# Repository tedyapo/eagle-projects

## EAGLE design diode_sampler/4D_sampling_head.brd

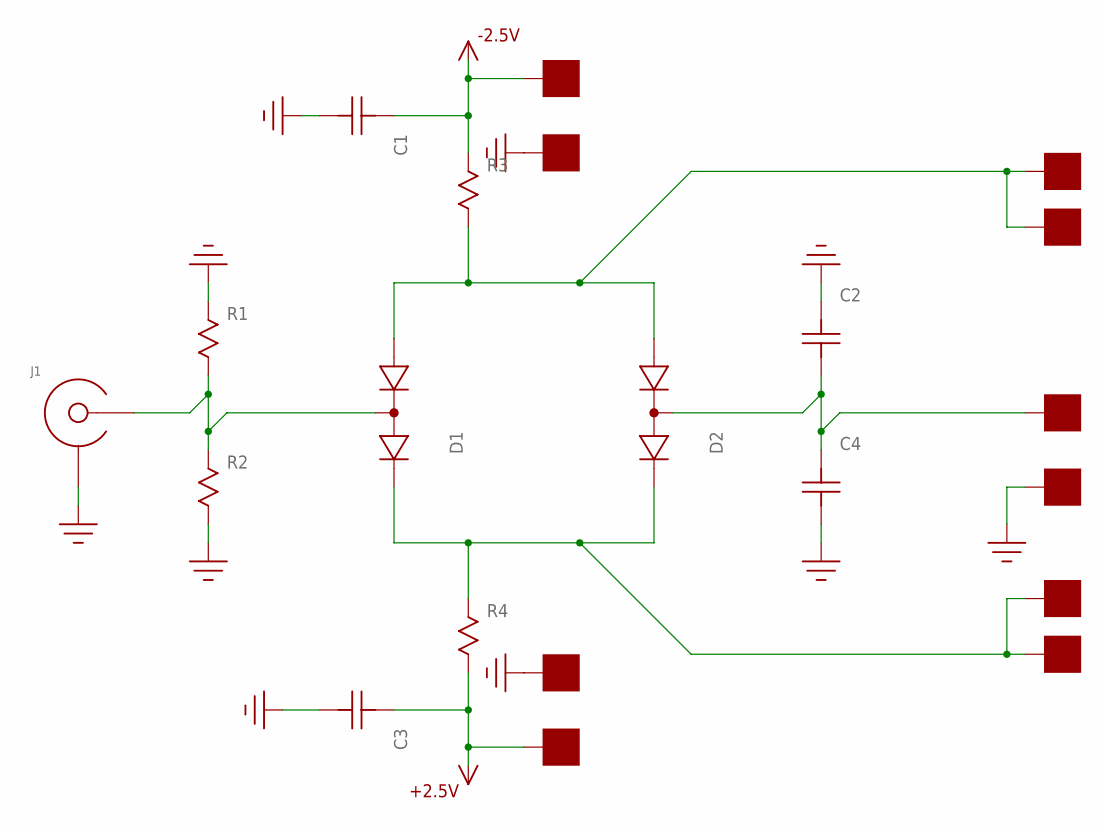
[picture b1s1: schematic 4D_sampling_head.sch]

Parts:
C1, C2, C3, C4: C0603
D1: MMBD352LT1G; SOT-23
D2: MMBD353LT1G; SOT-23
J1: EDGE_LAUNCH_JACK; EDGE_LAUNCH_RF_CON
R1, R2, R3, R4: R0603
U$11, U$12, U$13, U$14: PAD50MIL; PAD_50MIL
U$15, U$16, U$18, U$19, U$20, U$21: PAD100MIL; PAD_100MIL

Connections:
+2.5V: C3.P$2, R4.P$2, U$19.P$1
-2.5V: C1.P$2, R3.P$1, U$18.P$1
GND: C1.P$1, C2.P$2, C3.P$1, C4.P$1, J1.GND@1 (SHIELD), J1.GND@2 (SHIELD), J1.GND@3 (SHIELD), J1.GND@4 (SHIELD), J1.GND@5 (SHIELD), J1.GND@6 (SHIELD), J1.GND@7 (SHIELD), J1.GND@8 (SHIELD), J1.GND@9 (SHIELD), J1.GND@10 (SHIELD), J1.GND@11 (SHIELD), J1.GND@12 (SHIELD), J1.SHIELD@1 (SHIELD), J1.SHIELD@2 (SHIELD), R1.P$1, R2.P$2, U$16.P$1, U$20.P$1, U$21.P$1
unnamed: D1.3 (COMMON), J1.CENTER, R1.P$2, R2.P$1
unnamed: D1.2 (CATHODE), D2.1 (CATHODE), R4.P$1, U$12.P$1, U$14.P$1
unnamed: D1.1 (ANODE), D2.2 (ANODE), R3.P$2, U$11.P$1, U$13.P$1
unnamed: C2.P$1, C4.P$2, D2.3 (COMMON), U$15.P$1

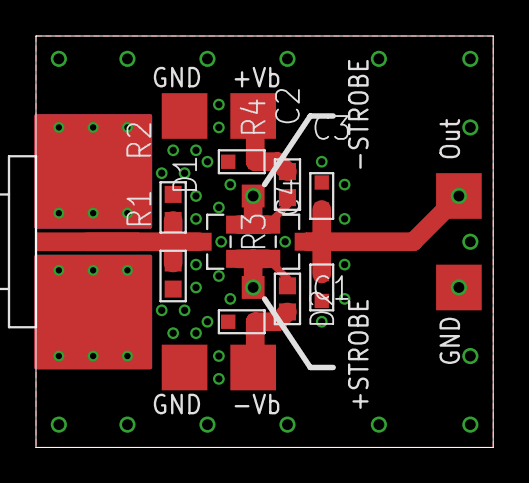
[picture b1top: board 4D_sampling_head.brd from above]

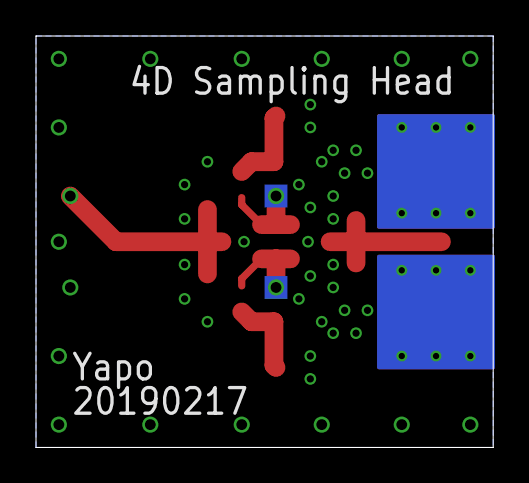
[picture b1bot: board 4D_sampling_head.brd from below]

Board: 2 copper layers, 25.4 x 22.9 mm, 21 parts (2 on the bottom side), 7 nets.

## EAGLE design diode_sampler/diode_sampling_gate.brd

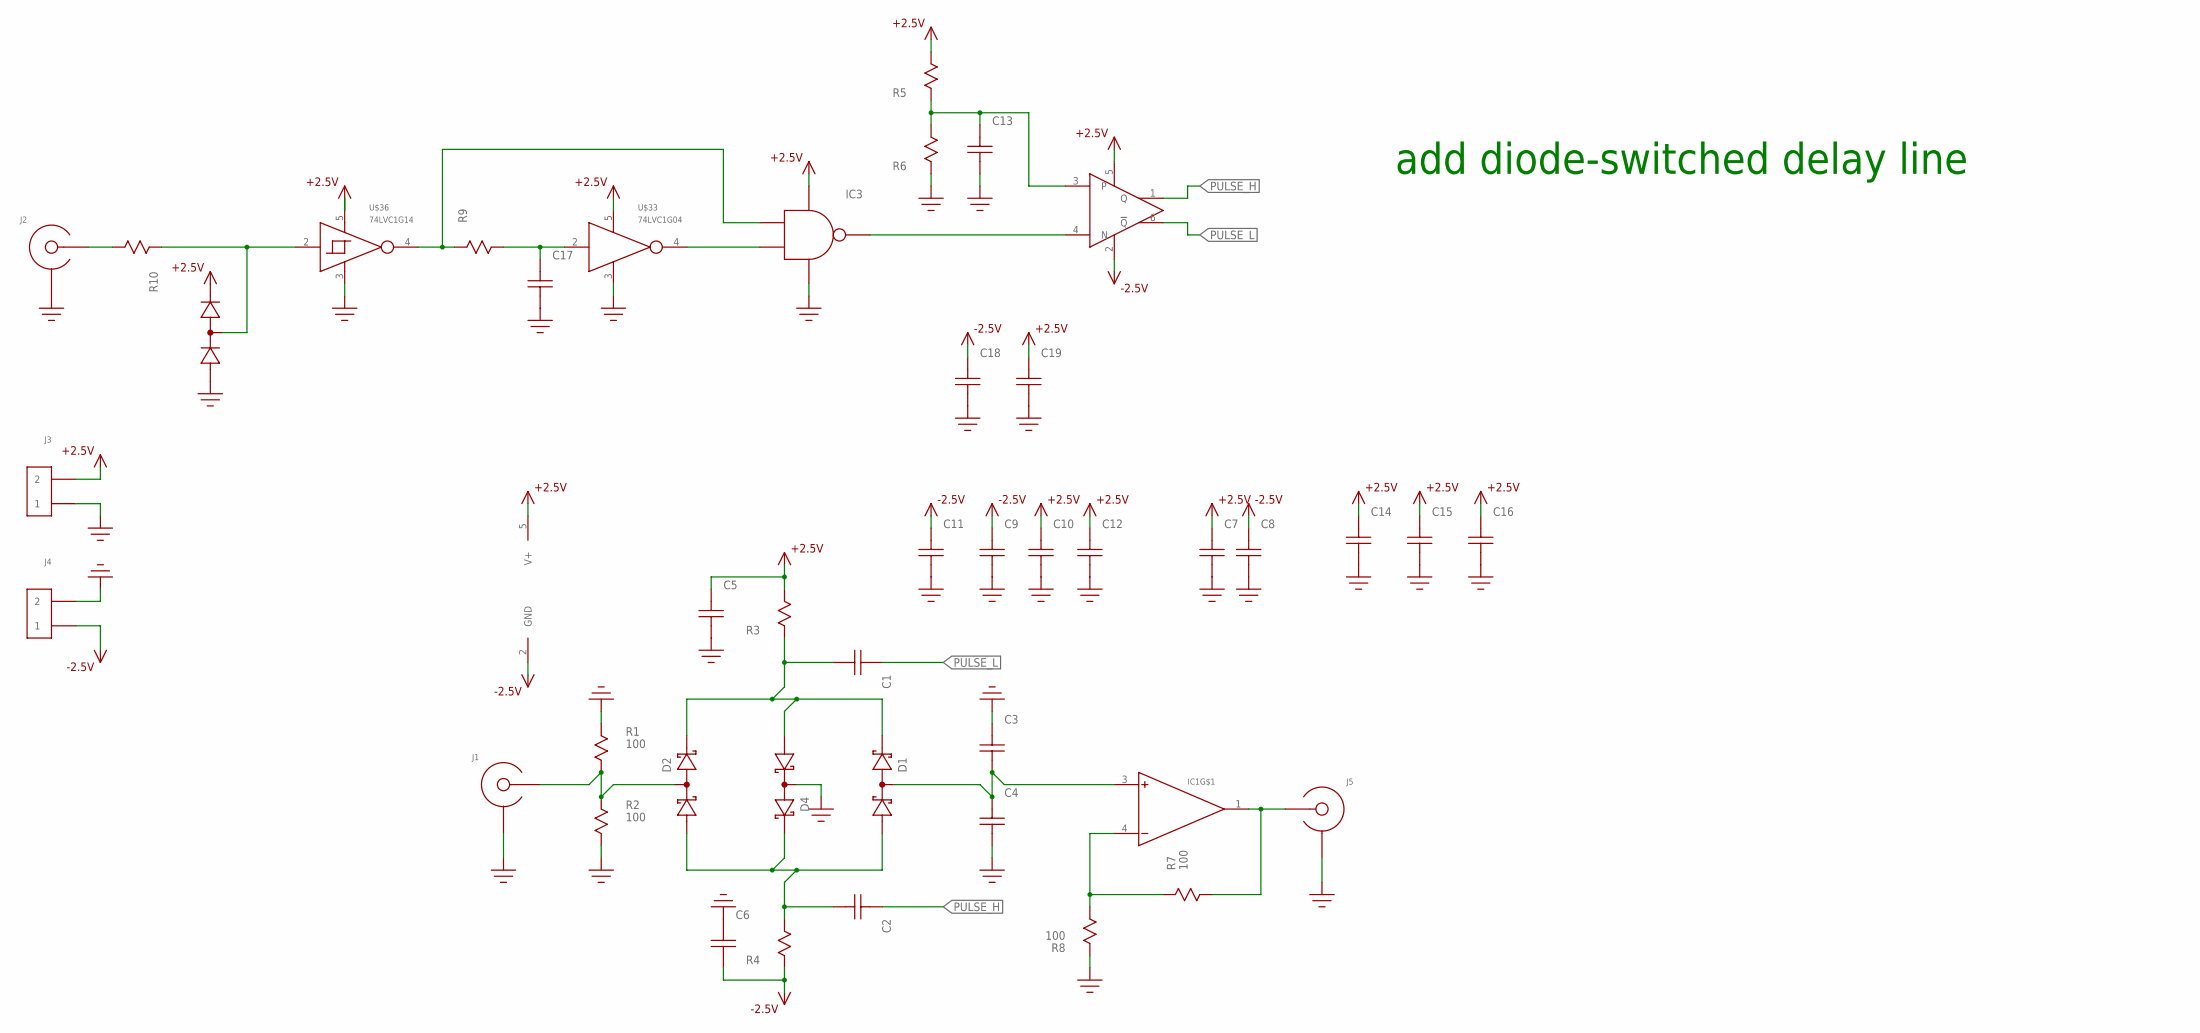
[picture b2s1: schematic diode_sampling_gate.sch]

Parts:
C1, C2, C3, C4, C5, C6, C9, C10, C13, C14, C15, C16, C17: C0603
C7, C8: C; C0402
C11, C12, C18, C19: C0805; 0805
D1, D2, D4: BAS40-04; SOT-23
IC1: MCP6V81; SOT23-5
IC2: ADCMP606; SC70-6
IC3: 74LVC1G00; SOT23-5
J1, J2, J5: EDGE_LAUNCH_JACK; EDGE_LAUNCH_RF_CON
J3, J4: HEADER_2PIN
R1, R2, R7, R8: 100; R0603
R3, R4, R5, R6, R9, R10: R0603
U$33: 74LVC1G04; SOT23-5
U$36: 74LVC1G14; SOT23-5
U$46: MMBD7000L; SOT-23

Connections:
+2.5V: C5.P$2, C7.2, C10.P$2, C12.P$2, C14.P$2, C15.P$2, C16.P$2, C19.P$2, IC1.5 (V+), IC2.5 (VCC), IC3.5 (VCC), J3.2, R3.P$2, R5.P$2, U$33.5 (VCC), U$36.5 (VCC), U$46.2 (CATHODE)
-2.5V: C6.P$1, C8.2, C9.P$2, C11.P$2, C18.P$2, IC1.2 (GND), IC2.2 (VEE), J4.1, R4.P$1
GND: C3.P$2, C4.P$1, C5.P$1, C6.P$2, C7.1, C8.1, C9.P$1, C10.P$1, C11.P$1, C12.P$1, C13.P$1, C14.P$1, C15.P$1, C16.P$1, C17.P$1, C18.P$1, C19.P$1, D4.3 (COMMON), IC3.3 (GND), J1.GND@1 (SHIELD), J1.GND@2 (SHIELD), J1.GND@3 (SHIELD), J1.GND@4 (SHIELD), J1.GND@5 (SHIELD), J1.GND@6 (SHIELD), J1.GND@7 (SHIELD), J1.GND@8 (SHIELD), J1.GND@9 (SHIELD), J1.GND@10 (SHIELD), J1.GND@11 (SHIELD), J1.GND@12 (SHIELD), J1.SHIELD@1 (SHIELD), J1.SHIELD@2 (SHIELD), J2.GND@1 (SHIELD), J2.GND@2 (SHIELD), J2.GND@3 (SHIELD), J2.GND@4 (SHIELD), J2.GND@5 (SHIELD), J2.GND@6 (SHIELD), J2.GND@7 (SHIELD), J2.GND@8 (SHIELD), J2.GND@9 (SHIELD), J2.GND@10 (SHIELD), J2.GND@11 (SHIELD), J2.GND@12 (SHIELD), J2.SHIELD@1 (SHIELD), J2.SHIELD@2 (SHIELD), J3.1, J4.2, J5.GND@1 (SHIELD), J5.GND@2 (SHIELD), J5.GND@3 (SHIELD), J5.GND@4 (SHIELD), J5.GND@5 (SHIELD), J5.GND@6 (SHIELD), J5.GND@7 (SHIELD), J5.GND@8 (SHIELD), J5.GND@9 (SHIELD), J5.GND@10 (SHIELD), J5.GND@11 (SHIELD), J5.GND@12 (SHIELD), J5.SHIELD@1 (SHIELD), J5.SHIELD@2 (SHIELD), R1.P$1, R2.P$2, R6.P$1, R8.P$1, U$33.3 (GND), U$36.3 (GND), U$46.1 (ANODE)
unnamed: D2.3 (COMMON), J1.CENTER, R1.P$2, R2.P$1
unnamed: C13.P$2, IC2.3, R5.P$1, R6.P$2
unnamed: C1.P$1, D1.2 (CATHODE), D2.2 (CATHODE), D4.1 (ANODE), R3.P$1
unnamed: IC2.4 (N), IC3.4 (Y)
unnamed: C2.P$1, D1.1 (ANODE), D2.1 (ANODE), D4.2 (CATHODE), R4.P$2
unnamed: IC1.4 (-), R7.P$1, R8.P$2
unnamed: IC1.1 (OUT), J5.CENTER, R7.P$2
unnamed: IC3.1 (B), U$33.4 (OUT)
unnamed: J2.CENTER, R10.P$2
unnamed: C3.P$1, C4.P$2, D1.3 (COMMON), IC1.3 (+)
unnamed: IC3.2 (A), R9.P$1, U$36.4 (OUT)
unnamed: C17.P$2, R9.P$2, U$33.2 (IN)
unnamed: R10.P$1, U$36.2 (IN), U$46.3 (COMMON)
PULSE_H: C2.P$2, IC2.1 (Q)
PULSE_L: C1.P$2, IC2.6 (!Q!)

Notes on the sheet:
add diode-switched delay line

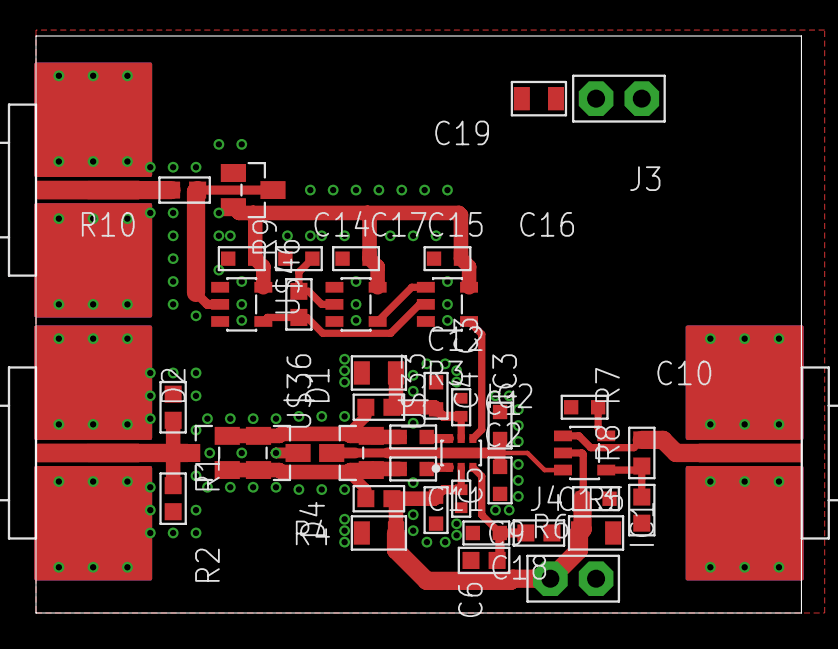
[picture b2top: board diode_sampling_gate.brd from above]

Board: 2 copper layers, 42.5 x 32.1 mm, 43 parts (0 on the bottom side), 18 nets.

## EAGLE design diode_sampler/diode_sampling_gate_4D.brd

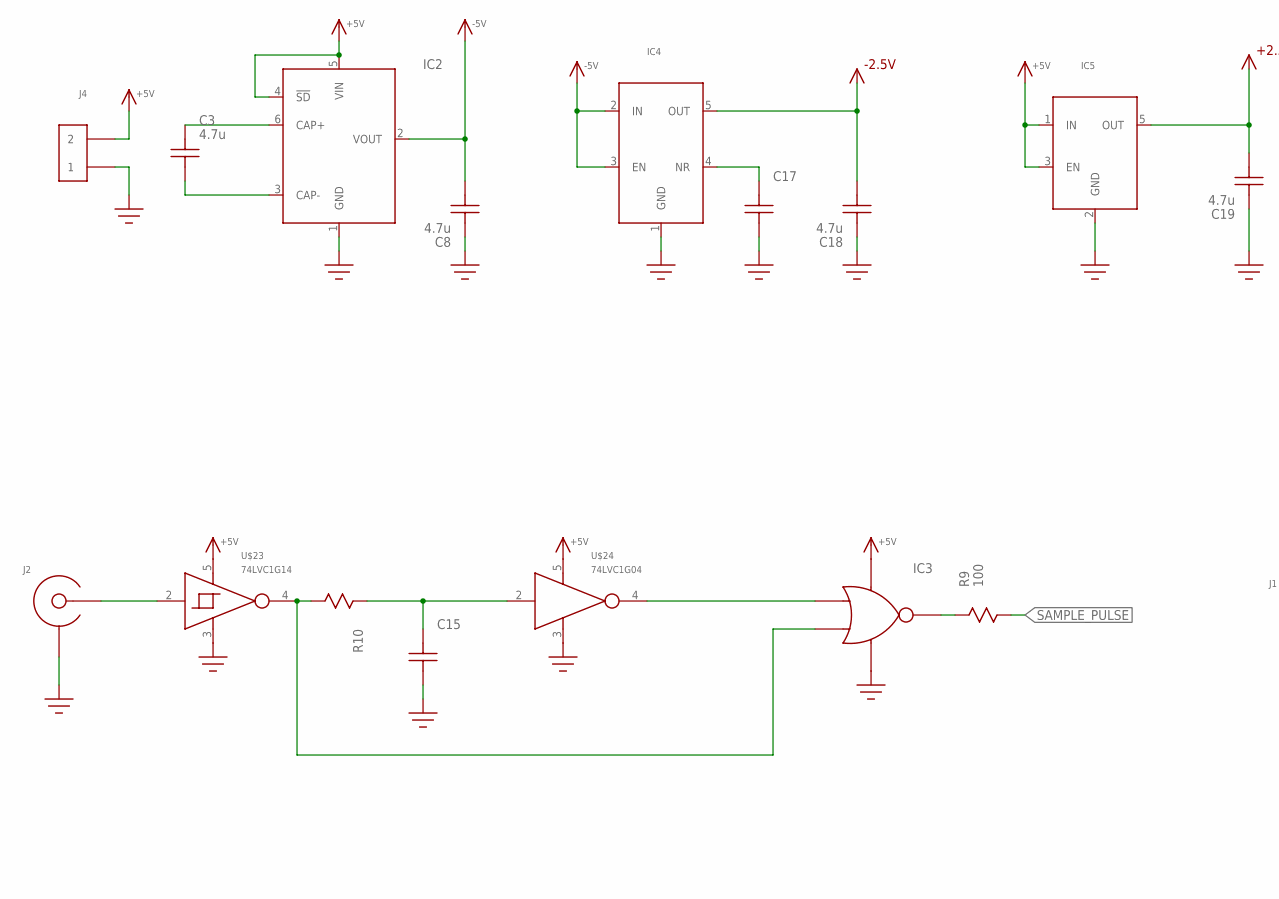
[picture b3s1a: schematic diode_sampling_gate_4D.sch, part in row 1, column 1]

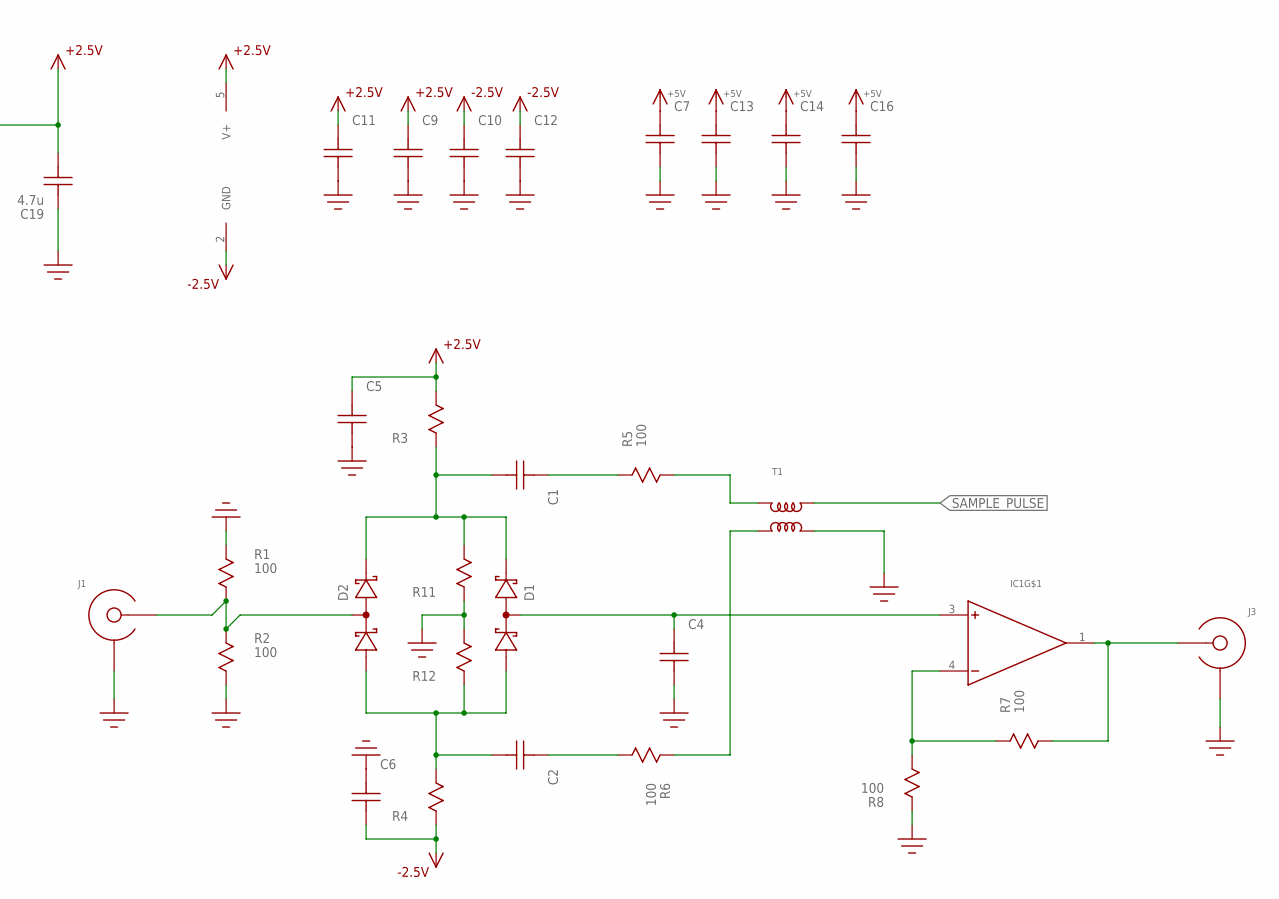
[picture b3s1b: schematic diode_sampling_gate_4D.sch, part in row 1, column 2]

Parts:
C1, C2, C4, C5, C6, C7, C9, C10, C13, C14, C15, C17: C0603
C3, C8, C18, C19: 4.7u; 0805
C11, C12, C16: C0805; 0805
D1, D2: BAS40-04; SOT-23
IC1: MCP6V81; SOT23-5
IC2: LM2664; SOT23-6
IC3: 74LVC1G02; SOT23-5
IC4: TPS723XX; SOT23-5
IC5: LP5907; SOT23-5
J1, J2, J3: EDGE_LAUNCH_JACK; EDGE_LAUNCH_RF_CON
J4: HEADER_2PIN
R1, R2, R5, R6, R7, R8, R9: 100; R0603
R3, R4, R10, R11, R12: R0603
T1: MABA007159; MABAES0061
U$23: 74LVC1G14; SOT23-5
U$24: 74LVC1G04; SOT23-5

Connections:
+2.5V: C5.P$2, C9.P$2, C11.P$2, C19.P$1, IC1.5 (V+), IC5.5 (OUT), R3.P$2
+5V: C7.P$2, C13.P$2, C14.P$2, C16.P$2, IC2.4 (!SD!), IC2.5 (VIN), IC3.5 (VCC), IC5.1 (IN), IC5.3 (EN), J4.2, U$23.5 (VCC), U$24.5 (VCC)
-2.5V: C6.P$1, C10.P$2, C12.P$2, C18.P$1, IC1.2 (GND), IC4.5 (OUT), R4.P$1
-5V: C8.P$1, IC2.2 (VOUT), IC4.2 (IN), IC4.3 (EN)
GND: C4.P$1, C5.P$1, C6.P$2, C7.P$1, C8.P$2, C9.P$1, C10.P$1, C11.P$1, C12.P$1, C13.P$1, C14.P$1, C15.P$1, C16.P$1, C17.P$1, C18.P$2, C19.P$2, IC2.1 (GND), IC3.3 (GND), IC4.1 (GND), IC5.2 (GND), J1.GND@1 (SHIELD), J1.GND@2 (SHIELD), J1.GND@3 (SHIELD), J1.GND@4 (SHIELD), J1.GND@5 (SHIELD), J1.GND@6 (SHIELD), J1.GND@7 (SHIELD), J1.GND@8 (SHIELD), J1.GND@9 (SHIELD), J1.GND@10 (SHIELD), J1.GND@11 (SHIELD), J1.GND@12 (SHIELD), J1.SHIELD@1 (SHIELD), J1.SHIELD@2 (SHIELD), J2.GND@1 (SHIELD), J2.GND@2 (SHIELD), J2.GND@3 (SHIELD), J2.GND@4 (SHIELD), J2.GND@5 (SHIELD), J2.GND@6 (SHIELD), J2.GND@7 (SHIELD), J2.GND@8 (SHIELD), J2.GND@9 (SHIELD), J2.GND@10 (SHIELD), J2.GND@11 (SHIELD), J2.GND@12 (SHIELD), J2.SHIELD@1 (SHIELD), J2.SHIELD@2 (SHIELD), J3.GND@1 (SHIELD), J3.GND@2 (SHIELD), J3.GND@3 (SHIELD), J3.GND@4 (SHIELD), J3.GND@5 (SHIELD), J3.GND@6 (SHIELD), J3.GND@7 (SHIELD), J3.GND@8 (SHIELD), J3.GND@9 (SHIELD), J3.GND@10 (SHIELD), J3.GND@11 (SHIELD), J3.GND@12 (SHIELD), J3.SHIELD@1 (SHIELD), J3.SHIELD@2 (SHIELD), J4.1, R1.P$1, R2.P$2, R8.P$1, R11.P$1, R12.P$2, T1.3, U$23.3 (GND), U$24.3 (GND)
unnamed: D2.3 (COMMON), J1.CENTER, R1.P$2, R2.P$1
unnamed: C1.P$2, R5.P$1
unnamed: C1.P$1, D1.2 (CATHODE), D2.2 (CATHODE), R3.P$1, R11.P$2
unnamed: IC3.2 (B), R10.P$2, U$23.4 (OUT)
unnamed: C2.P$1, D1.1 (ANODE), D2.1 (ANODE), R4.P$2, R12.P$1
unnamed: IC1.4 (-), R7.P$1, R8.P$2
unnamed: IC1.1 (OUT), J3.CENTER, R7.P$2
unnamed: IC3.1 (A), U$24.4 (OUT)
unnamed: C2.P$2, R6.P$2
unnamed: C4.P$2, D1.3 (COMMON), IC1.3 (+)
unnamed: R5.P$2, T1.5
unnamed: R6.P$1, T1.4
unnamed: C17.P$2, IC4.4 (NR)
unnamed: C15.P$2, R10.P$1, U$24.2 (IN)
unnamed: IC3.4 (Y), R9.P$1
unnamed: J2.CENTER, U$23.2 (IN)
unnamed: C3.P$2, IC2.6 (CAP+)
unnamed: C3.P$1, IC2.3 (CAP-)
SAMPLE_PULSE: R9.P$2, T1.1

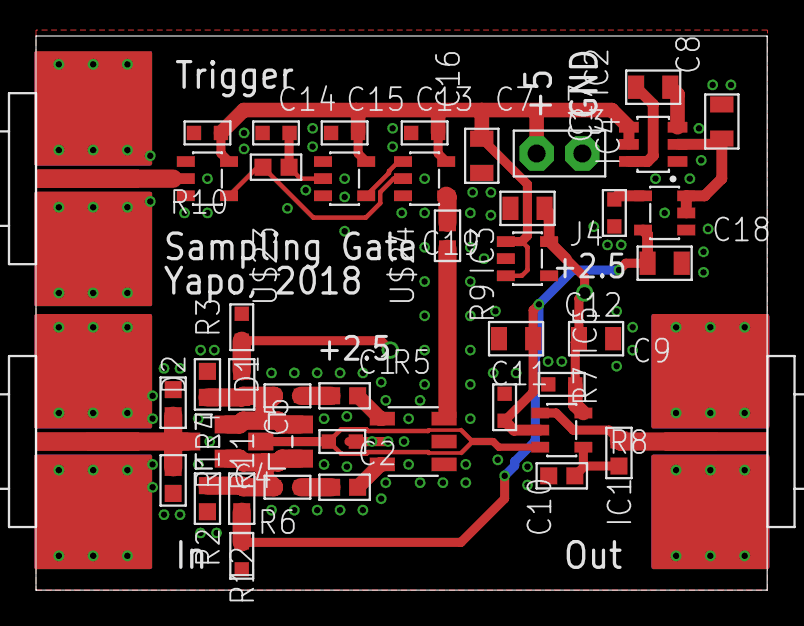
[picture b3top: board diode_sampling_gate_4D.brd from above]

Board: 2 copper layers, 40.6 x 30.8 mm, 45 parts (0 on the bottom side), 24 nets.

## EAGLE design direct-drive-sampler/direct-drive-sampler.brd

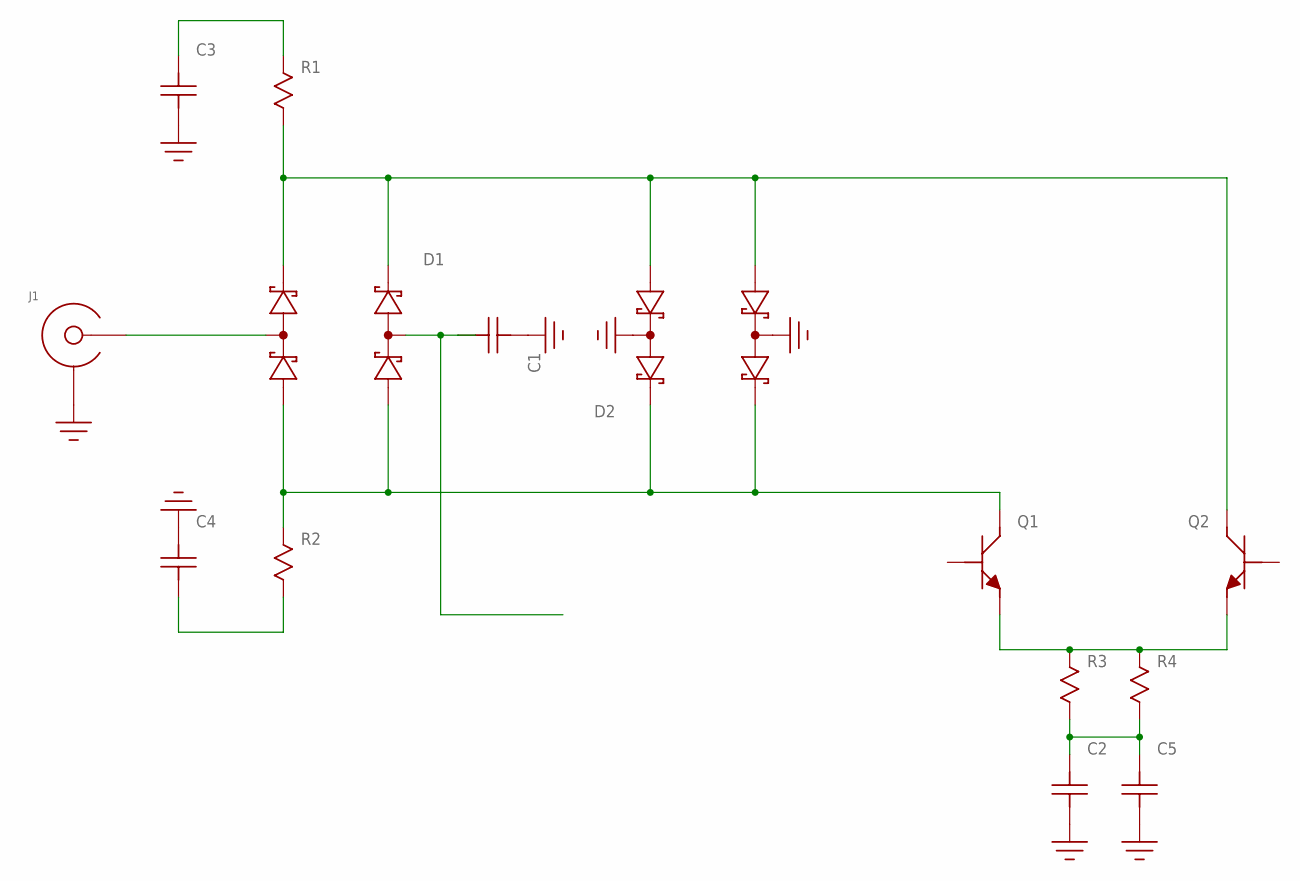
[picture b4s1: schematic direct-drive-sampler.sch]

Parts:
C1, C2, C3, C4, C5: C; C0402
D1, D2: SMS3923-081; SC-88
J1: SMA-EDGE-LAUNCH; SMA_EDGE_LAUNCH_2L_4020_TAPER_FIXED
Q1, Q2: NPN-BFP740; SOT343
R1, R2, R3, R4: R0402; 0402

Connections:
GND: C1.2, C2.1, C3.1, C4.2, C5.1, D2.2 (COMMON0), D2.5 (COMMON1), J1.BOTTOM_GND (SHIELD), J1.GND@1 (SHIELD), J1.GND@2 (SHIELD), J1.GND@3 (SHIELD), J1.GND@4 (SHIELD), J1.GND@5 (SHIELD), J1.GND@6 (SHIELD), J1.GND@7 (SHIELD), J1.GND@8 (SHIELD), J1.GND@14 (SHIELD), J1.GND@15 (SHIELD), J1.GND@16 (SHIELD), J1.GND@17 (SHIELD), J1.GND_PAD1 (SHIELD), J1.GND_PAD2 (SHIELD), J1.P$1 (SHIELD), J1.P$2 (SHIELD)
unnamed: D1.5 (COMMON1), J1.CENTER@1 (CENTER), J1.P$3 (CENTER)
unnamed: C1.1, D1.2 (COMMON0)
unnamed: D1.3 (CATHODE0), D1.4 (CATHODE1), D2.1 (ANODE0), D2.6 (ANODE1), Q2.3 (C), R1.2
unnamed: D1.1 (ANODE0), D1.6 (ANODE1), D2.3 (CATHODE0), D2.4 (CATHODE1), Q1.3 (C), R2.1
unnamed: C3.2, R1.1
unnamed: C4.1, R2.2
unnamed: Q1.2 (E), Q1.4 (E), Q2.2 (E), Q2.4 (E), R3.1, R4.1
unnamed: C2.2, C5.2, R3.2, R4.2

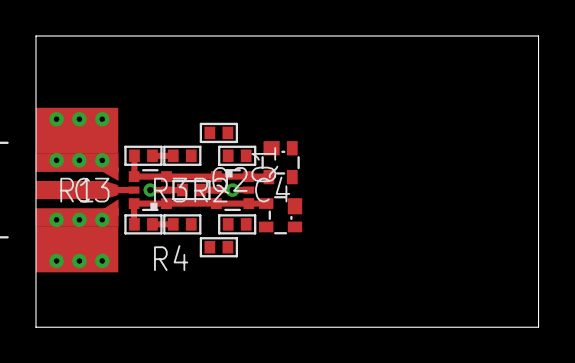
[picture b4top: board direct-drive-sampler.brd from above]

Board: 2 copper layers, 27.9 x 16.2 mm, 14 parts (0 on the bottom side), 9 nets.

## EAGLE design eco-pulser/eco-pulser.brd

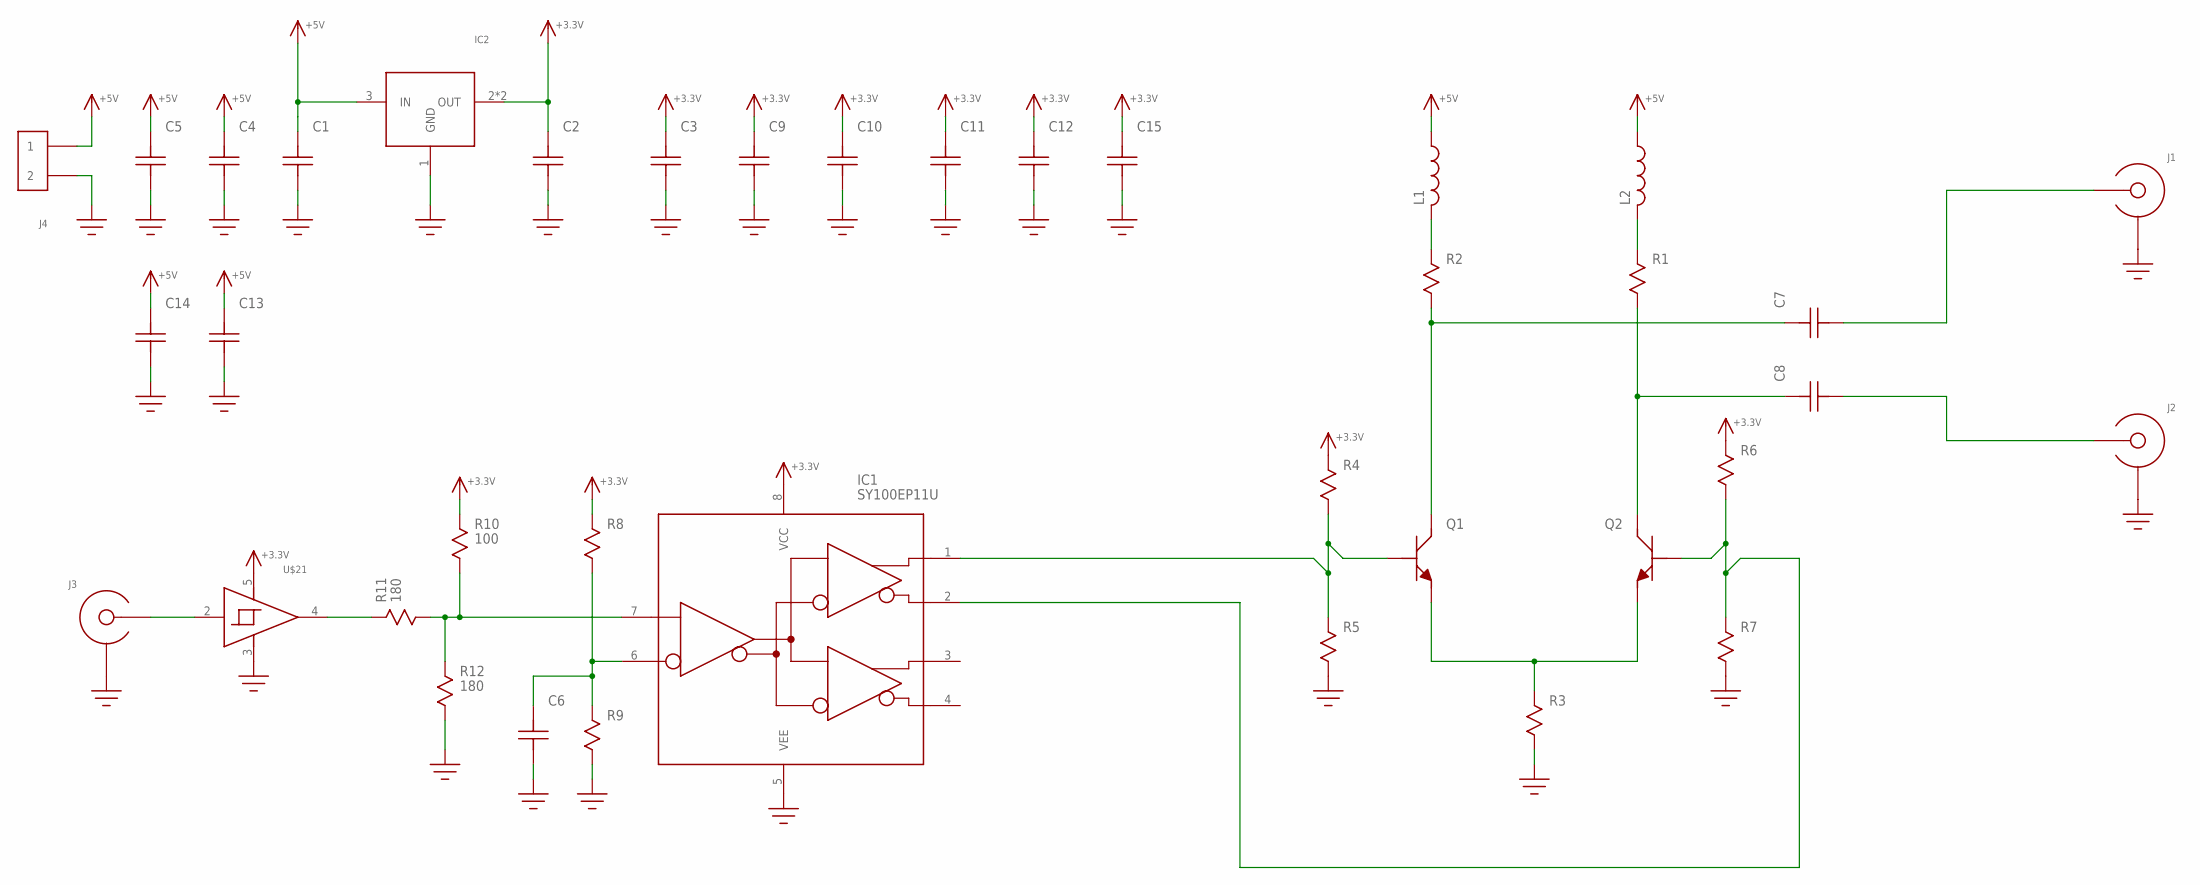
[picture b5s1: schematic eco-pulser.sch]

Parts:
C1, C2: C1206; 1206
C3, C4, C5, C6, C7, C8, C9, C10, C11, C12, C13, C14, C15: C0603
IC1: SY100EP11U; SOIC8
IC2: AZ1117E; SOT-223
J1, J2, J3: SMA_END_LAUNCH4L; SMA_EDGE_LAUNCH
J4: HEADER_2PIN
L1, L2: INDUCTOR; R0603
Q1, Q2: NPN-BFP740; SOT343
R1, R2, R3, R4, R5, R6, R7, R8, R9: R0603
R10: 100; R0603
R11, R12: 180; R0603
U$21: 74LVC1G17; SOT23-5

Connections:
+3.3V: C2.P$2, C3.P$2, C9.P$2, C10.P$2, C11.P$2, C12.P$2, C15.P$2, IC1.8 (VCC), IC2.2 (OUT), IC2.4 (OUT), R4.P$1, R6.P$1, R8.P$1, R10.P$1, U$21.5 (VCC)
+5V: C1.P$2, C4.P$2, C5.P$2, C13.P$2, C14.P$2, IC2.3 (IN), J4.1, L1.P$1 (1), L2.P$1 (1)
GND: C1.P$1, C2.P$1, C3.P$1, C4.P$1, C5.P$1, C6.P$1, C9.P$1, C10.P$1, C11.P$1, C12.P$1, C13.P$1, C14.P$1, C15.P$1, IC1.5 (VEE), IC2.1 (GND), J1.BOTTOM_PAD (SHIELD), J1.GND@1 (SHIELD), J1.GND@2 (SHIELD), J1.GND@3 (SHIELD), J1.GND@4 (SHIELD), J1.GND@5 (SHIELD), J1.GND@6 (SHIELD), J1.GND@7 (SHIELD), J1.GND@8 (SHIELD), J1.GND@14 (SHIELD), J1.GND@15 (SHIELD), J1.GND@16 (SHIELD), J1.GND@17 (SHIELD), J1.GND_PAD1 (SHIELD), J1.GND_PAD2 (SHIELD), J2.BOTTOM_PAD (SHIELD), J2.GND@1 (SHIELD), J2.GND@2 (SHIELD), J2.GND@3 (SHIELD), J2.GND@4 (SHIELD), J2.GND@5 (SHIELD), J2.GND@6 (SHIELD), J2.GND@7 (SHIELD), J2.GND@8 (SHIELD), J2.GND@14 (SHIELD), J2.GND@15 (SHIELD), J2.GND@16 (SHIELD), J2.GND@17 (SHIELD), J2.GND_PAD1 (SHIELD), J2.GND_PAD2 (SHIELD), J3.BOTTOM_PAD (SHIELD), J3.GND@1 (SHIELD), J3.GND@2 (SHIELD), J3.GND@3 (SHIELD), J3.GND@4 (SHIELD), J3.GND@5 (SHIELD), J3.GND@6 (SHIELD), J3.GND@7 (SHIELD), J3.GND@8 (SHIELD), J3.GND@14 (SHIELD), J3.GND@15 (SHIELD), J3.GND@16 (SHIELD), J3.GND@17 (SHIELD), J3.GND_PAD1 (SHIELD), J3.GND_PAD2 (SHIELD), J4.2, R3.P$2, R5.P$2, R7.P$2, R9.P$2, R12.P$2, U$21.3 (GND)
unnamed: L1.P$2 (2), R2.P$1
unnamed: L2.P$2 (2), R1.P$1
unnamed: C7.P$2, Q1.3 (C), R2.P$2
unnamed: C8.P$2, Q2.3 (C), R1.P$2
unnamed: Q1.2 (E), Q1.4 (E), Q2.2 (E), Q2.4 (E), R3.P$1
unnamed: IC1.1 (Q0), Q1.1 (B), R4.P$2, R5.P$1
unnamed: C6.P$2, IC1.6 (!D!), R8.P$2, R9.P$1
unnamed: IC1.2 (!Q0!), Q2.1 (B), R6.P$2, R7.P$1
unnamed: R11.P$1, U$21.4 (OUT)
unnamed: IC1.7 (D), R10.P$2, R11.P$2, R12.P$1
unnamed: J3.CENTER@1 (CENTER), J3.CENTER@2 (CENTER), U$21.2 (IN)
unnamed: C7.P$1, J1.CENTER@1 (CENTER), J1.CENTER@2 (CENTER)
unnamed: C8.P$1, J2.CENTER@1 (CENTER), J2.CENTER@2 (CENTER)

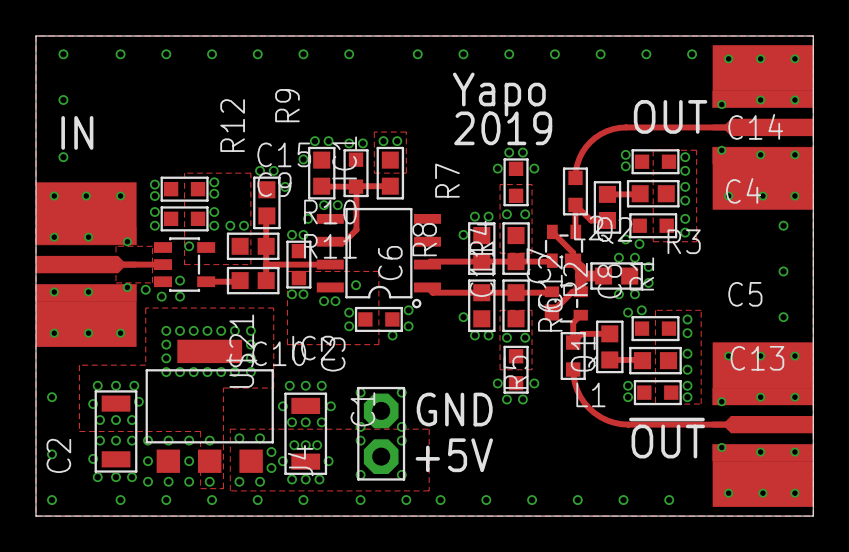
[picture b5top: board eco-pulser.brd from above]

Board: 4 copper layers, 43.2 x 26.7 mm, 38 parts (0 on the bottom side), 16 nets.

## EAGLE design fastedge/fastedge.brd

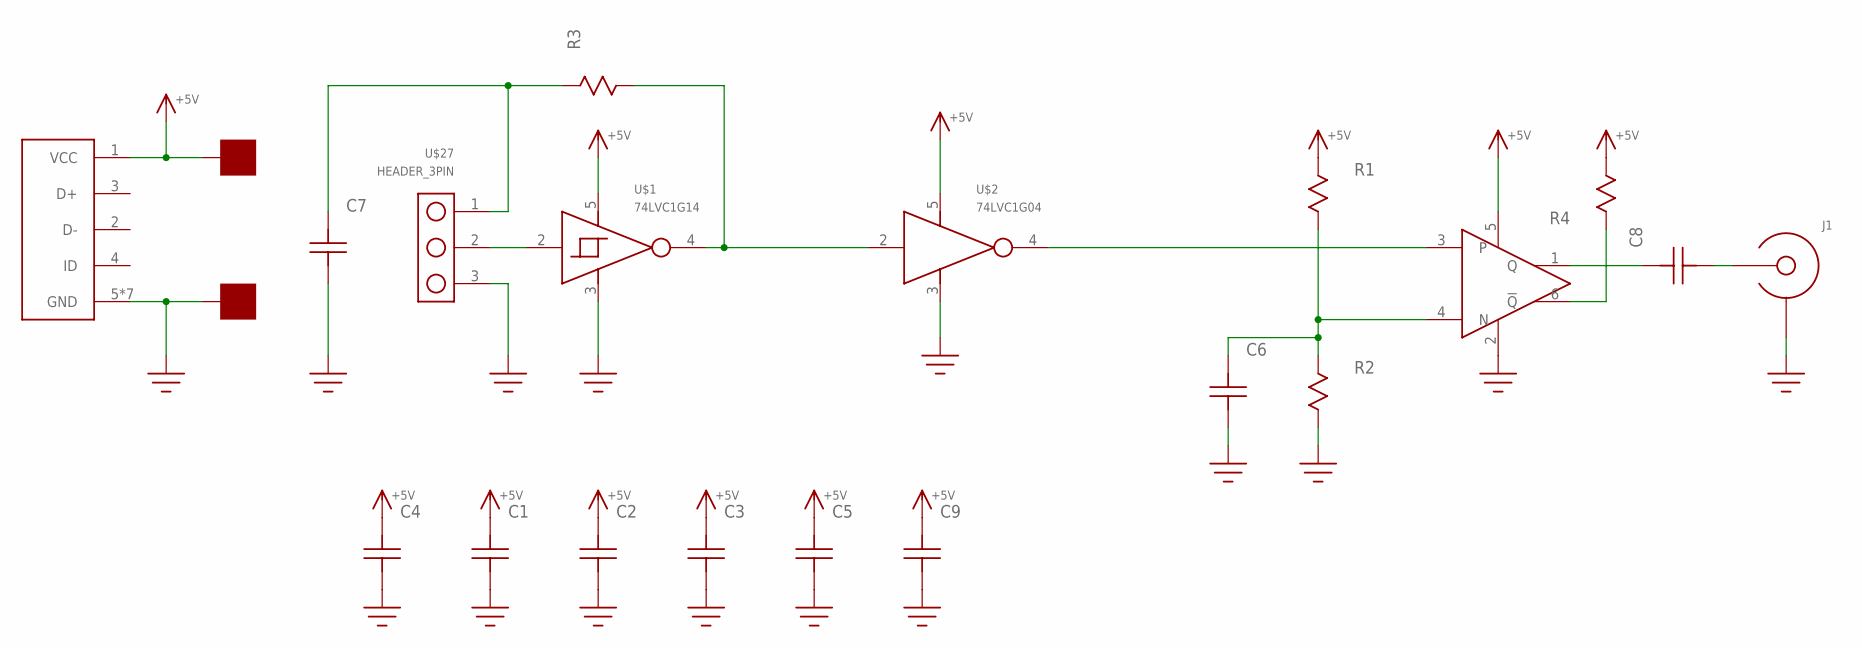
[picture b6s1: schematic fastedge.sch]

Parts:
C1, C2, C3, C6, C7: C0603
C4: C0805; 0805
C5, C8, C9: C0402_NO_THERMALS
IC1: ADCMP606; SC70-6
J1: BNC_MALE_PCB
R1, R2, R3: R0603
R4: R0402; 0402
U$1: 74LVC1G14; SOT23-5
U$2: 74LVC1G04; SOT23-5
U$13: USB_JACK; FCI_MICRO_USB
U$27: HEADER_3PIN
U$32, U$33: PAD50MIL; PAD_50MIL

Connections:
+5V: C1.P$2, C2.P$2, C3.P$2, C4.P$2, C5.2, C9.2, IC1.5 (VCC), R1.P$1, R4.2, U$1.5 (VCC), U$2.5 (VCC), U$13.1 (VCC), U$32.P$1
GND: C1.P$1, C2.P$1, C3.P$1, C4.P$1, C5.1, C6.P$1, C7.P$1, C9.1, IC1.2 (VEE), J1.SHIELD@1 (SHIELD), J1.SHIELD@2 (SHIELD), J1.SHIELD@3 (SHIELD), J1.SHIELD@4 (SHIELD), R2.P$2, U$1.3 (GND), U$2.3 (GND), U$13.5 (GND), U$13.GND1 (GND), U$13.GND2 (GND), U$13.GND3 (GND), U$13.GND4 (GND), U$13.GND5 (GND), U$13.GND6 (GND), U$27.3, U$33.P$1
unnamed: C6.P$2, IC1.4 (N), R1.P$2, R2.P$1
unnamed: C7.P$2, R3.P$1, U$27.1
unnamed: IC1.3, U$2.4 (OUT)
unnamed: R3.P$2, U$1.4 (OUT), U$2.2 (IN)
unnamed: U$1.2 (IN), U$27.2
unnamed: C8.2, IC1.1 (Q)
unnamed: IC1.6 (!Q!), R4.1
unnamed: C8.1, J1.CENTER

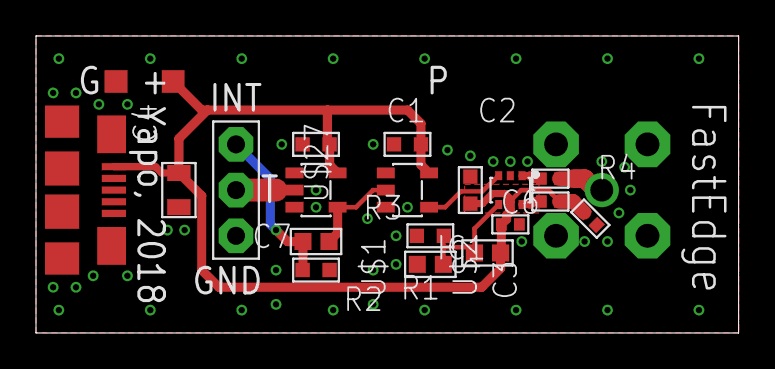
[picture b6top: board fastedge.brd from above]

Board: 2 copper layers, 39.0 x 16.5 mm, 21 parts (0 on the bottom side), 10 nets.
